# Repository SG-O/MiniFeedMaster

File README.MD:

# Mainboard for automated SMT Feeder system #

## Documentation ##

You can find the manufacturing documentation [here.](https://github.com/SG-O/MiniFeedMaster/tree/master/Doc)

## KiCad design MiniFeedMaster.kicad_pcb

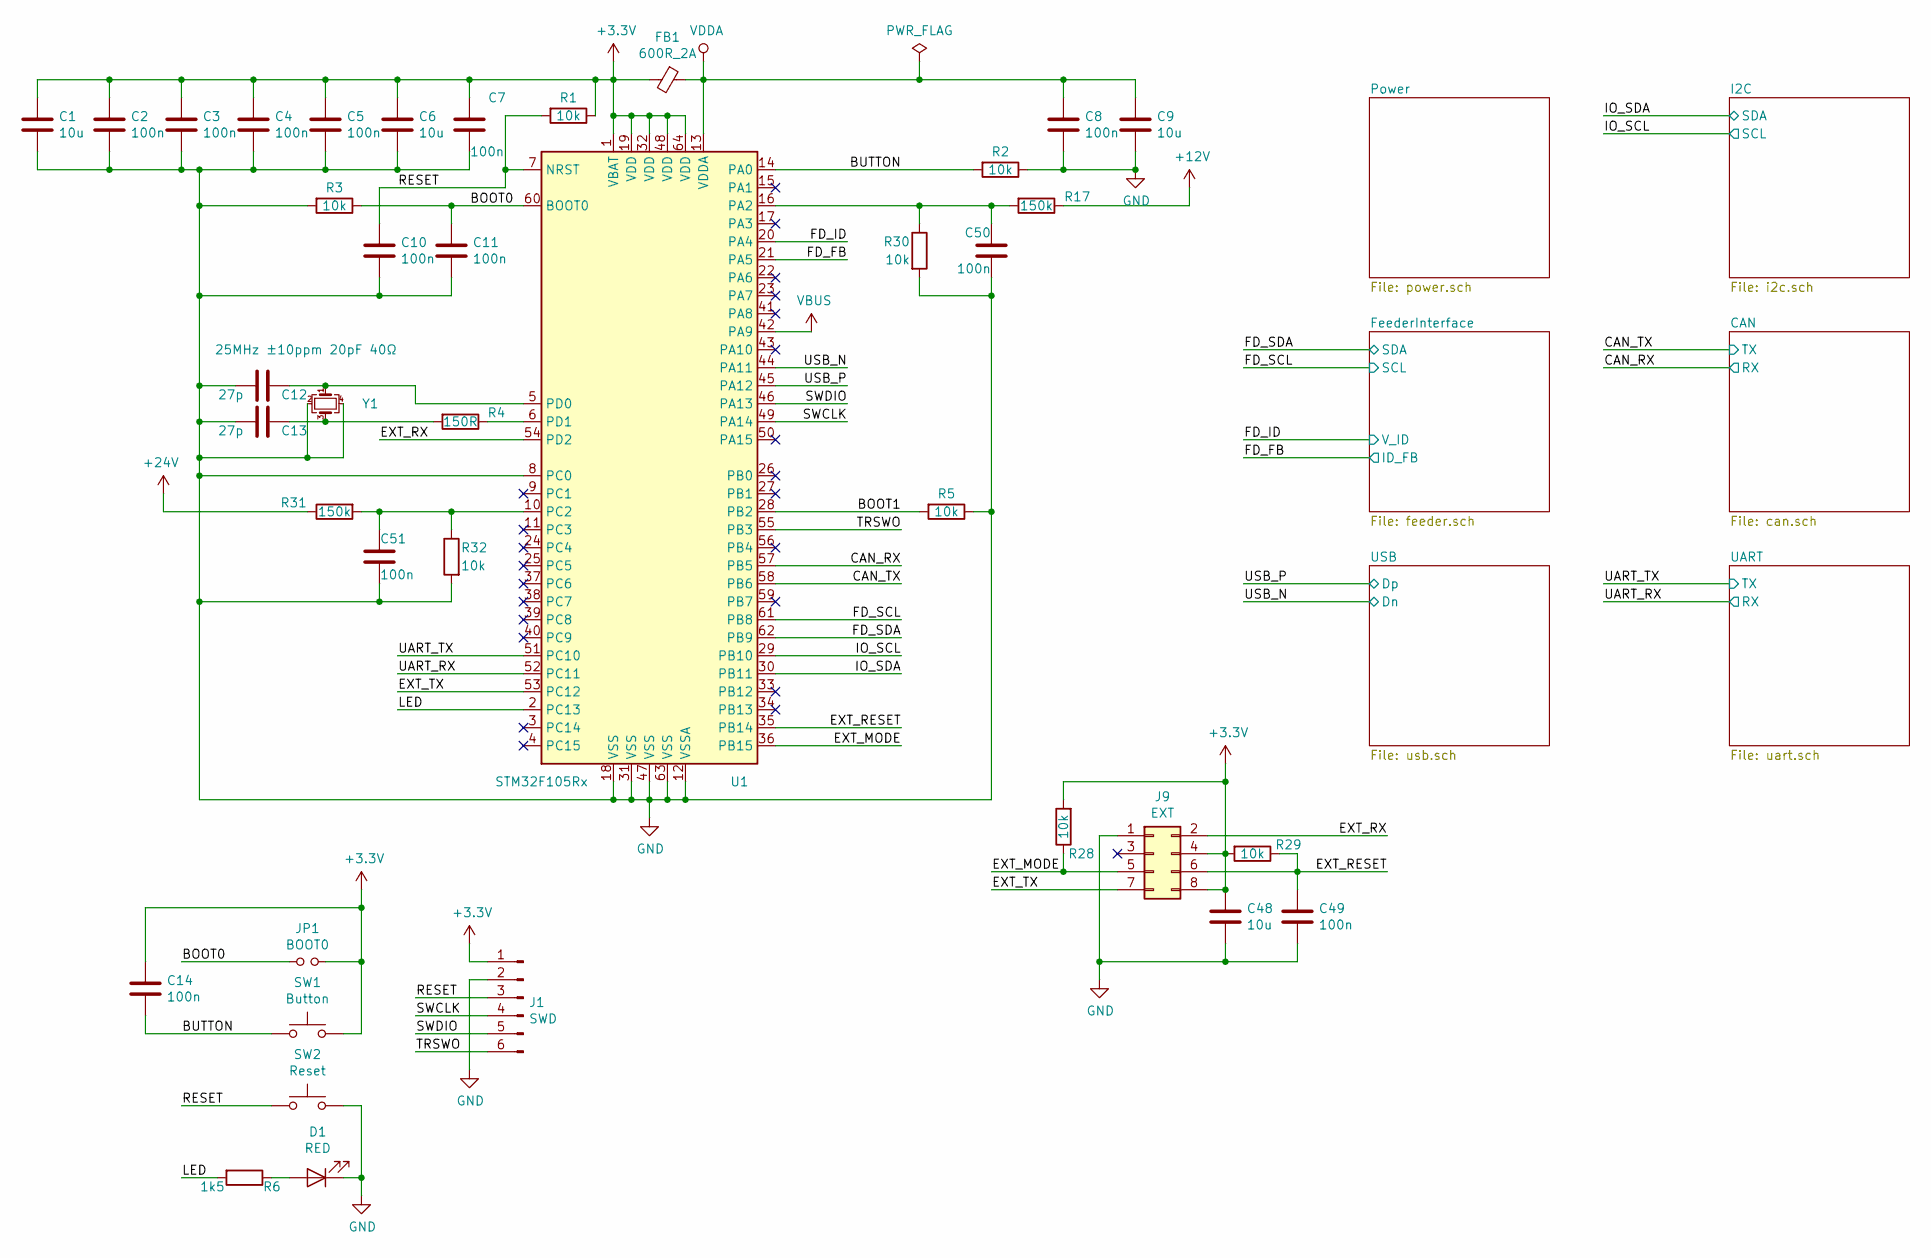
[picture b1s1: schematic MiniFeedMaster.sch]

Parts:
C1, C6, C9, C48: 10u; C_1206_3216Metric; lcsc# C14860
C2, C3, C4, C5, C7, C8, C10, C11, C14, C49, C50, C51: 100n; C_0603_1608Metric; lcsc# C1591
C12, C13: 27p; C_0603_1608Metric; lcsc# C107045
D1: RED; LED_0603_1608Metric; lcsc# C118330
FB1: 600R_2A; L_0805_2012Metric; lcsc# C81034
J1: SWD; PinSocket_1x06_P1.27mm_Vertical
J9: EXT; PinSocket_2x04_P2.54mm_Vertical; lcsc# C92271
JP1: BOOT0; SolderJumper-2_P1.3mm_Open_RoundedPad1.0x1.5mm
R1, R2, R3, R5, R28, R29, R30, R32: 10k; R_0603_1608Metric; lcsc# C128781
R4: 150R; R_0603_1608Metric; lcsc# C319856
R6: 1k5; R_0805_2012Metric; lcsc# C118217
R17, R31: 150k; R_0603_1608Metric; lcsc# C311920
SW1: Button; SW_SPST_SKQG_WithStem; lcsc# C318889
SW2: Reset; SW_SPST_SKQG_WithStem; lcsc# C318889
U1: STM32F105Rx; LQFP-64_10x10mm_P0.5mm; lcsc# C80986
Y1: 25MHz ±10ppm 20pF 40Ω; Crystal_SMD_3225-4Pin_3.2x2.5mm; lcsc# C709159

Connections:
+3V3: C1.1, C2.1, C3.1, C4.1, C5.1, C6.1, C7.1, C14.1, C48.1, FB1.2, J1.1, J9.4, J9.8, JP1.2, R1.1, R28.2, R29.2, SW1.2, U1.1 (VBAT), U1.19 (VDD), U1.32 (VDD), U1.48 (VDD), U1.64 (VDD); also elsewhere on the board
+12V: R17.1; also elsewhere on the board
+24V: R31.1; also elsewhere on the board
/BOOT0: C11.1, JP1.1, R3.1, U1.60 (BOOT0)
/BOOT1: R5.2, U1.28 (PB2)
/BUTTON: C14.2, R2.2, SW1.1, U1.14 (PA0)
/CAN_RX: U1.57 (PB5); also elsewhere on the board
/CAN_TX: U1.58 (PB6); also elsewhere on the board
/EXT_MODE: J9.5, R28.1, U1.36 (PB15)
/EXT_RESET: C49.1, J9.6, R29.1, U1.35 (PB14)
/EXT_RX: J9.2, U1.54 (PD2)
/EXT_TX: J9.7, U1.53 (PC12)
/FD_FB: U1.21 (PA5); also elsewhere on the board
/FD_ID: U1.20 (PA4); also elsewhere on the board
/FD_SCL: U1.61 (PB8); also elsewhere on the board
/FD_SDA: U1.62 (PB9); also elsewhere on the board
/IO_SCL: U1.29 (PB10); also elsewhere on the board
/IO_SDA: U1.30 (PB11); also elsewhere on the board
/LED: R6.2, U1.2 (PC13)
/RESET: C10.1, J1.3, R1.2, SW2.1, U1.7 (NRST)
/SWCLK: J1.4, U1.49 (PA14)
/SWDIO: J1.5, U1.46 (PA13)
/TRSWO: J1.6, U1.55 (PB3)
/UART_RX: U1.52 (PC11); also elsewhere on the board
/UART_TX: U1.51 (PC10); also elsewhere on the board
/USB_N: U1.44 (PA11); also elsewhere on the board
/USB_P: U1.45 (PA12); also elsewhere on the board
GND: C1.2, C2.2, C3.2, C4.2, C5.2, C6.2, C7.2, C8.2, C9.2, C10.2, C11.2, C12.2, C13.2, C48.2, C49.2, C50.2, C51.2, D1.1 (K), J1.2, J9.1, R2.1, R3.2, R5.1, R30.2, R32.2, SW2.2, U1.8 (PC0), U1.12 (VSSA), U1.18 (VSS), U1.31 (VSS), U1.47 (VSS), U1.63 (VSS), Y1.2, Y1.4; also elsewhere on the board
unnamed: C12.1, U1.5 (PD0), Y1.1
unnamed: C13.1, R4.2, Y1.3
unnamed: C50.1, R17.2, R30.1, U1.16 (PA2)
unnamed: C51.1, R31.2, R32.1, U1.10 (PC2)
unnamed: D1.2 (A), R6.1
unnamed: R4.1, U1.6 (PD1)
VBUS: U1.42 (PA9); also elsewhere on the board
VDDA: C8.1, C9.1, FB1.1, U1.13 (VDDA)

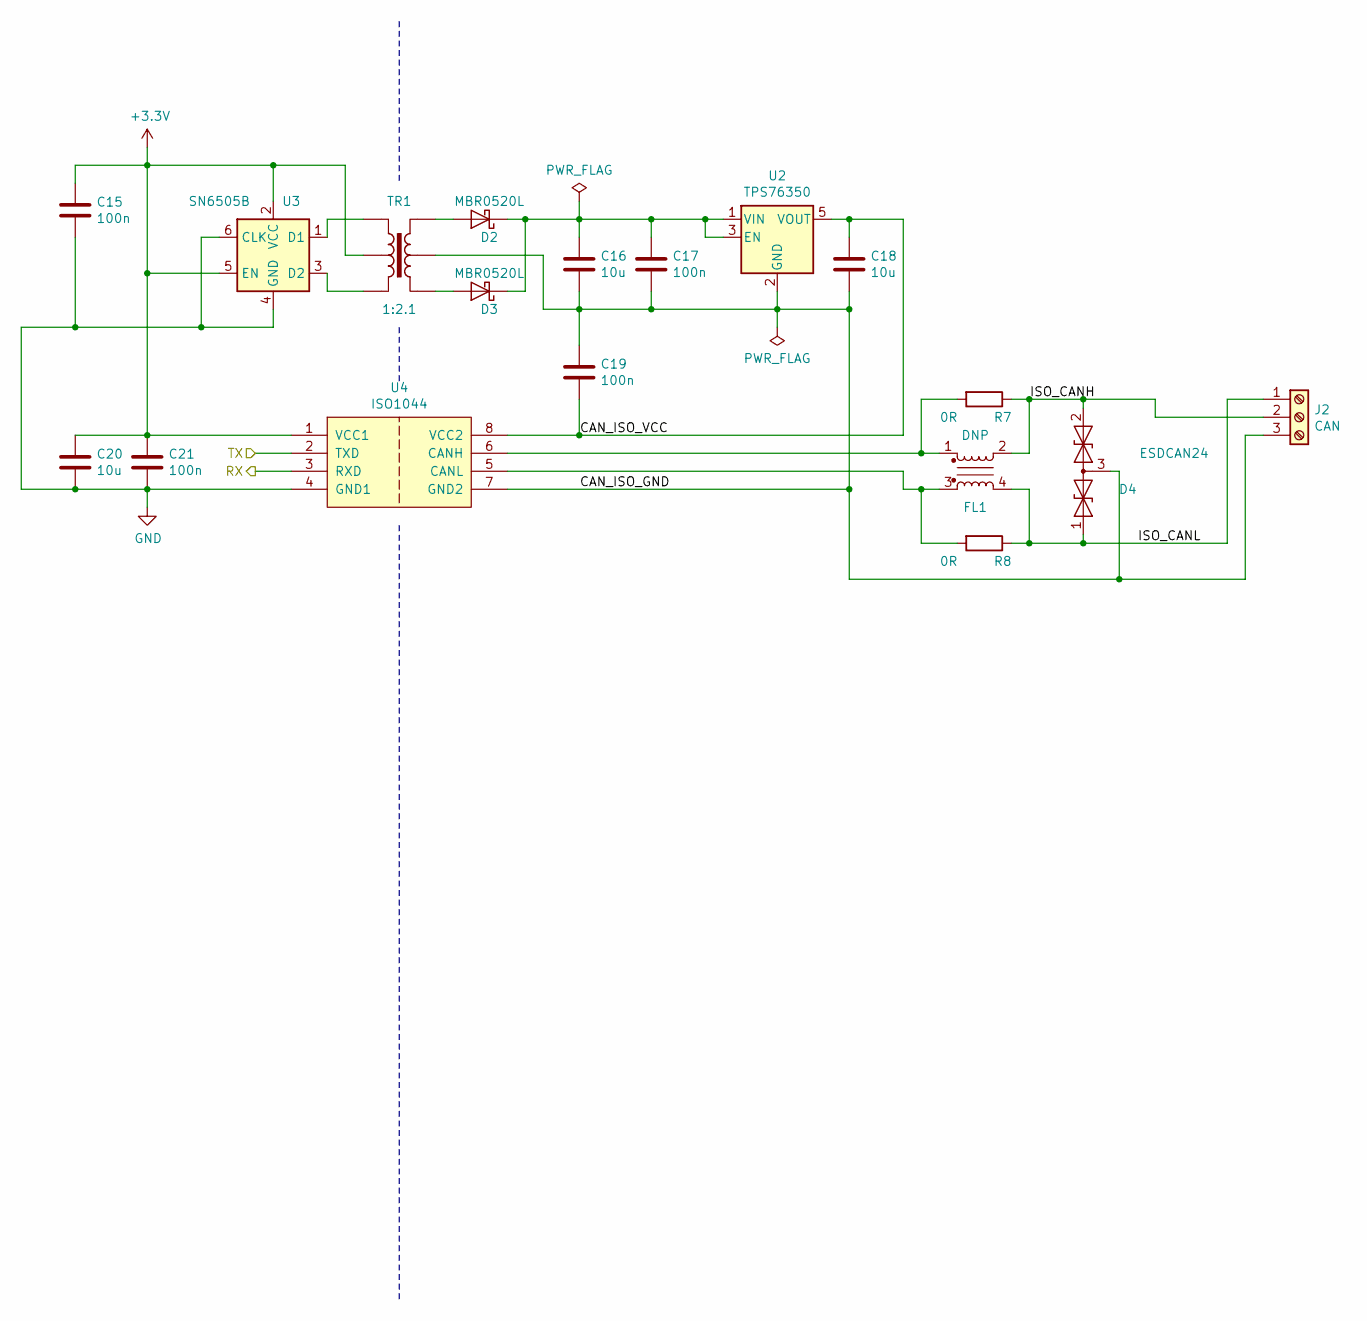
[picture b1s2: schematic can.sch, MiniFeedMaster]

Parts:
C15, C17, C19, C21: 100n; C_0603_1608Metric; lcsc# C1591
C16, C18, C20: 10u; C_1206_3216Metric; lcsc# C14860
D2, D3: MBR0520L; D_SOD-123; lcsc# C23848
D4: ESDCAN24; SOT-23; lcsc# C246766
FL1: DNP; FIL_ACT45B-510-2P-TL003; lcsc# C76584
J2: CAN; TerminalBlock_KaiFeng_KF141R-3_1x03_P2.54mm; lcsc# C475125
R7, R8: 0R; R_0603_1608Metric; lcsc# C163836
TR1: 1:2.1; TOROID_SMD_6PIN_(1109)
U2: TPS76350; SOT-23-5; lcsc# C194609
U3: SN6505B; SOT-23-6; lcsc# C74518
U4: ISO1044; SOIC-8_3.9x4.9mm_P1.27mm

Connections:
+3V3: C15.1, C20.1, C21.1, TR1.2, U3.2 (VCC), U3.5 (EN), U4.1 (VCC1); also elsewhere on the board
/CAN/CAN_ISO_GND: C16.2, C17.2, C18.2, C19.1, D4.3 (common), J2.3, TR1.5, U2.2 (GND), U4.7 (GND2)
/CAN/CAN_ISO_VCC: C18.1, C19.2, U2.5 (VOUT), U4.8 (VCC2)
/CAN/ISO_CANH: D4.2 (A2), FL1.2, J2.2, R7.1
/CAN/ISO_CANL: D4.1 (A1), FL1.4, J2.1, R8.1
/CAN_RX: U4.3 (RXD); also elsewhere on the board
/CAN_TX: U4.2 (TXD); also elsewhere on the board
GND: C15.2, C20.2, C21.2, U3.4 (GND), U3.6 (CLK), U4.4 (GND1); also elsewhere on the board
unnamed: C16.1, C17.1, D2.1 (K), D3.1 (K), U2.1 (VIN), U2.3 (EN)
unnamed: D2.2 (A), TR1.4
unnamed: D3.2 (A), TR1.6
unnamed: FL1.1, R7.2, U4.6 (CANH)
unnamed: FL1.3, R8.2, U4.5 (CANL)
unnamed: TR1.1, U3.3 (D2)
unnamed: TR1.3, U3.1 (D1)

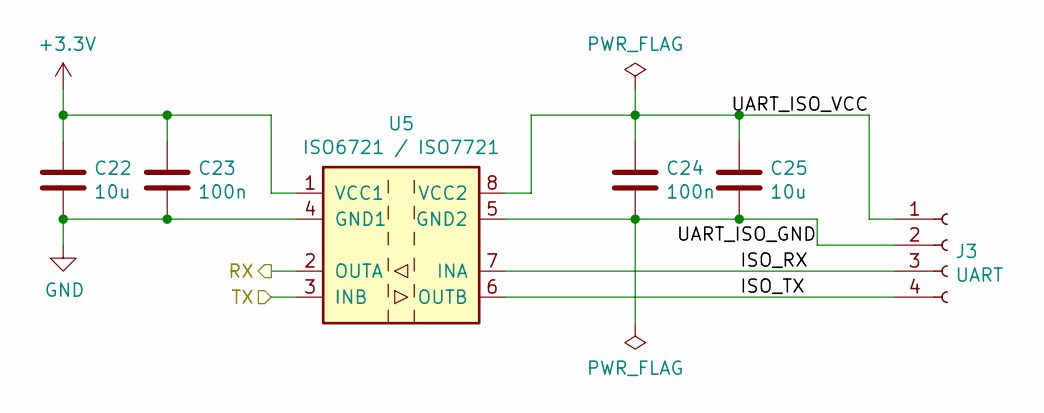
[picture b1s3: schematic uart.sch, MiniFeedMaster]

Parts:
C22, C25: 10u; C_1206_3216Metric; lcsc# C14860
C23, C24: 100n; C_0603_1608Metric; lcsc# C1591
J3: UART; TerminalBlock_KaiFeng_KF141R-4_1x04_P2.54mm; lcsc# C475126
U5: ISO6721 / ISO7721; SOIC-8_3.9x4.9mm_P1.27mm; lcsc# C366164

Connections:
+3V3: C22.1, C23.1, U5.1 (VCC1); also elsewhere on the board
/UART/ISO_RX: J3.3, U5.7 (INA)
/UART/ISO_TX: J3.4, U5.6 (OUTB)
/UART/UART_ISO_GND: C24.2, C25.2, J3.2, U5.5 (GND2)
/UART/UART_ISO_VCC: C24.1, C25.1, J3.1, U5.8 (VCC2)
/UART_RX: U5.2 (OUTA); also elsewhere on the board
/UART_TX: U5.3 (INB); also elsewhere on the board
GND: C22.2, C23.2, U5.4 (GND1); also elsewhere on the board

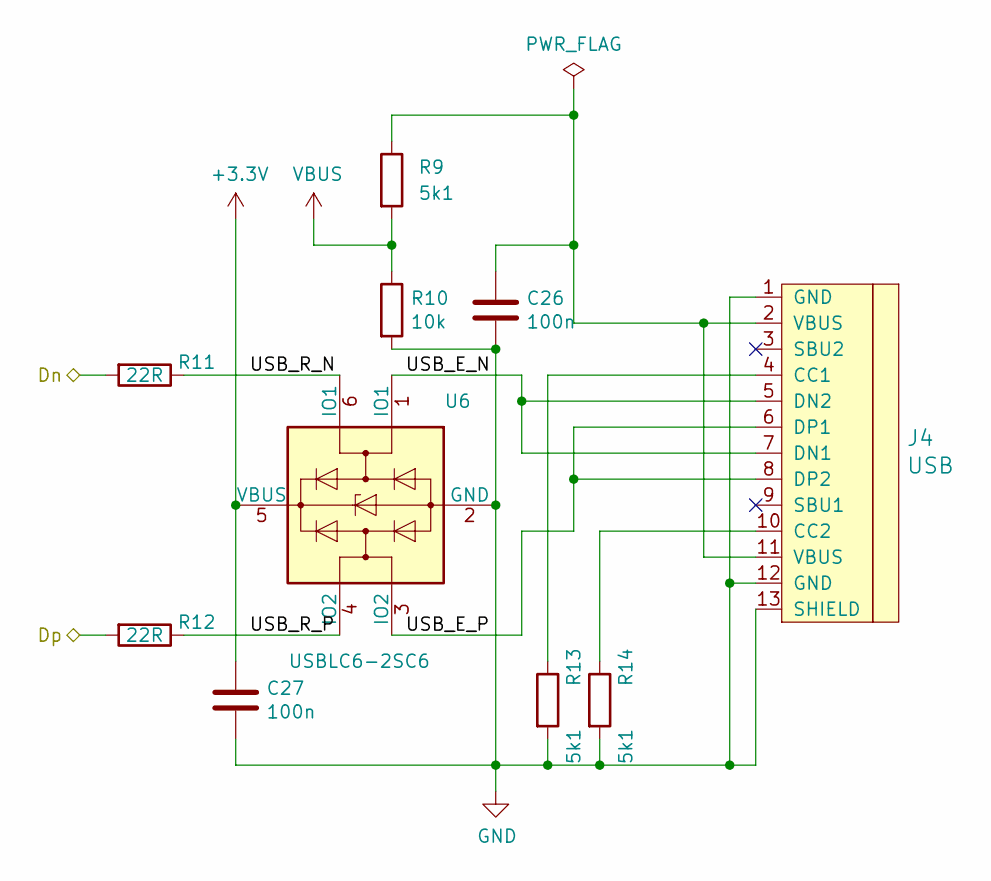
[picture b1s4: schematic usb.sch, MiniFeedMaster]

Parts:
C26, C27: 100n; C_0603_1608Metric; lcsc# C1591
J4: USB; HRO-TYPE-C-31-M-12-Assembly; lcsc# C165948
R9, R13, R14: 5k1; R_0603_1608Metric; lcsc# C425650
R10: 10k; R_0603_1608Metric; lcsc# C128781
R11, R12: 22R; R_0603_1608Metric; lcsc# C186356
U6: USBLC6-2SC6; SOT-23-6; lcsc# C558442

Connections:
+3V3: C27.1, U6.5 (VBUS); also elsewhere on the board
/USB/USB_E_N: J4.5 (DN2), J4.7 (DN1), U6.1 (IO1)
/USB/USB_E_P: J4.6 (DP1), J4.8 (DP2), U6.3 (IO2)
/USB/USB_R_N: R11.1, U6.6 (IO1)
/USB/USB_R_P: R12.1, U6.4 (IO2)
/USB_N: R11.2; also elsewhere on the board
/USB_P: R12.2; also elsewhere on the board
GND: C26.2, C27.2, J4.1 (GND), J4.12 (GND), J4.13 (SHIELD), R10.2, R13.2, R14.2, U6.2 (GND); also elsewhere on the board
unnamed: C26.1, J4.2 (VBUS), J4.11 (VBUS), R9.1
unnamed: J4.4 (CC1), R13.1
unnamed: J4.10 (CC2), R14.1
VBUS: R9.2, R10.1; also elsewhere on the board

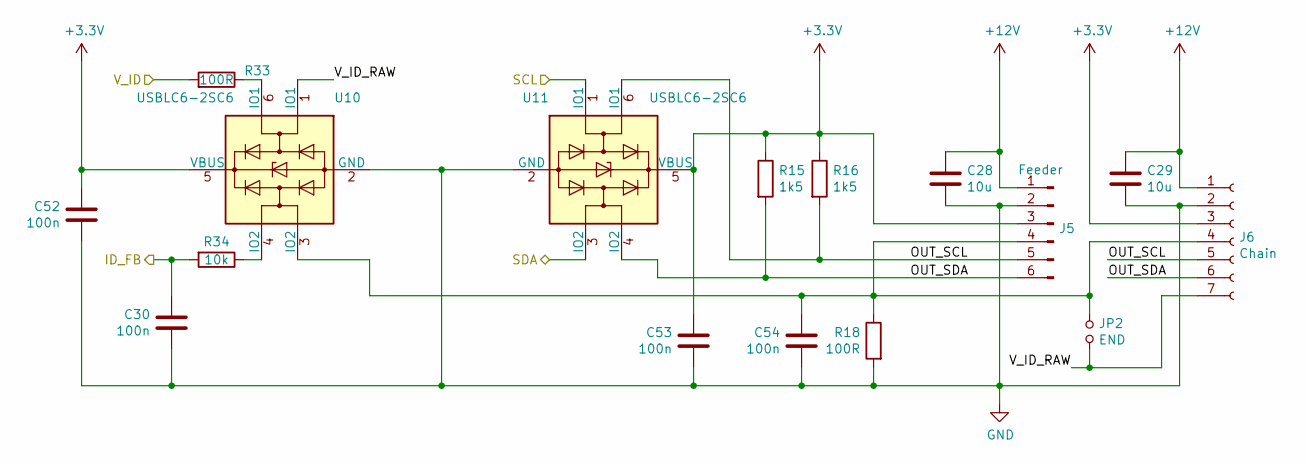
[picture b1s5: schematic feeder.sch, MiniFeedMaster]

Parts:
C28, C29: 10u; C_1206_3216Metric; lcsc# C14860
C30, C52, C53, C54: 100n; C_0603_1608Metric; lcsc# C1591
J5: Feeder; PogoEdgeConnector
J6: Chain; PinSocket_1x07_P2.54mm_Horizontal; lcsc# C225515
JP2: END; PinHeader_1x02_P2.54mm_Horizontal; lcsc# C376120;C5305
R15, R16: 1k5; R_0805_2012Metric; lcsc# C118217
R18, R33: 100R; R_0603_1608Metric; lcsc# C217683
R34: 10k; R_0603_1608Metric; lcsc# C128781
U10, U11: USBLC6-2SC6; SOT-23-6; lcsc# C558442

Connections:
+3V3: C52.1, C53.1, J5.3, J6.3, R15.1, R16.1, U10.5 (VBUS), U11.5 (VBUS); also elsewhere on the board
+12V: C28.1, C29.1, J5.1, J6.1; also elsewhere on the board
/FD_FB: C30.1, R34.2; also elsewhere on the board
/FD_ID: R33.2; also elsewhere on the board
/FD_SCL: U11.1 (IO1); also elsewhere on the board
/FD_SDA: U11.3 (IO2); also elsewhere on the board
/FeederInterface/OUT_SCL: J5.5, J6.5, R16.2, U11.6 (IO1)
/FeederInterface/OUT_SDA: J5.6, J6.6, R15.2, U11.4 (IO2)
/FeederInterface/V_ID_RAW: J6.7, JP2.2, U10.1 (IO1)
GND: C28.2, C29.2, C30.2, C52.2, C53.2, C54.2, J5.2, J6.2, R18.2, U10.2 (GND), U11.2 (GND); also elsewhere on the board
unnamed: C54.1, J5.4, J6.4, JP2.1, R18.1, U10.3 (IO2)
unnamed: R33.1, U10.6 (IO1)
unnamed: R34.1, U10.4 (IO2)

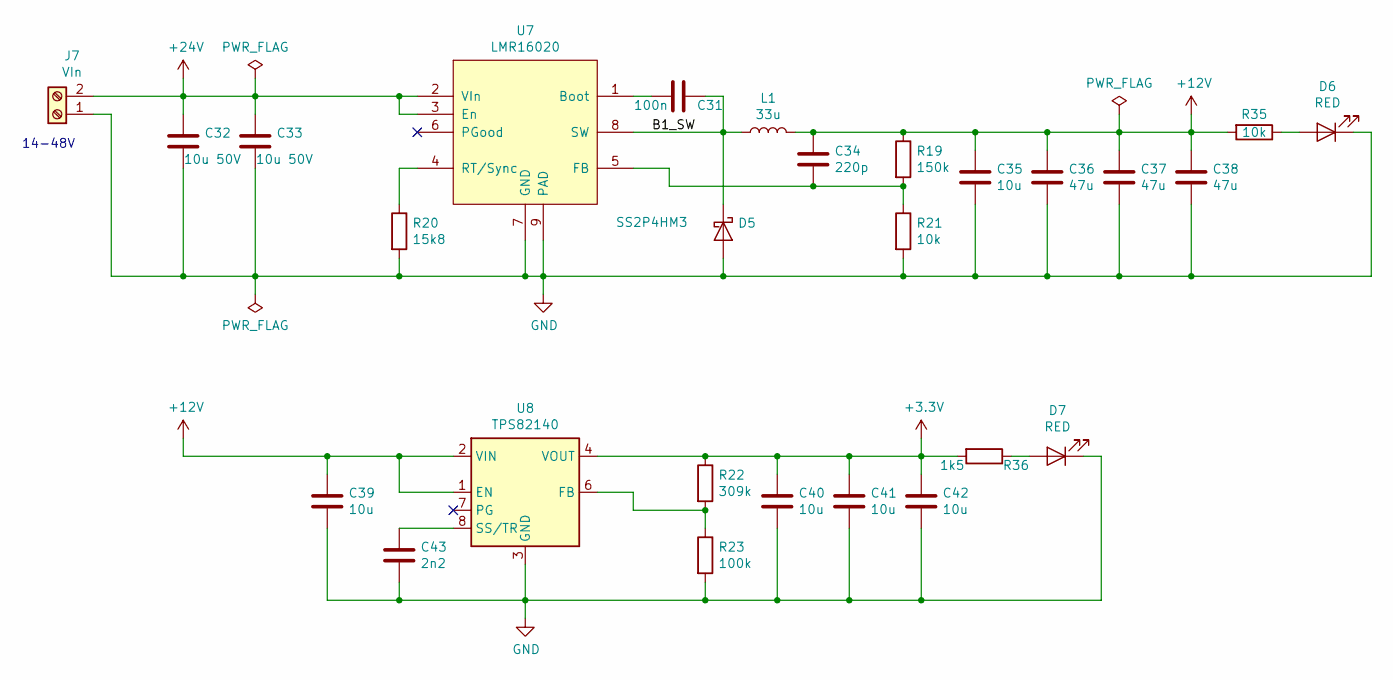
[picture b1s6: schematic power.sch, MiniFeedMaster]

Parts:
C31: 100n; C_0603_1608Metric; lcsc# C1591
C32, C33: 10u 50V; C_1210_3225Metric; lcsc# C337485
C34: 220p; C_0603_1608Metric; lcsc# C27675
C35, C39, C40, C41, C42: 10u; C_1206_3216Metric; lcsc# C14860
C36, C37, C38: 47u; C_2220_5650Metric; lcsc# C342293
C43: 2n2; C_0603_1608Metric; lcsc# C16033
D5: SS2P4HM3; DO-220AA; lcsc# C467996
D6, D7: RED; LED_0603_1608Metric; lcsc# C118330
J7: VIn; PhoenixContact_MC_1,5_2-G-3.81_1x02_P3.81mm_Horizontal; lcsc# C8387;C8466
L1: 33u; Inductor10x10mm; lcsc# C253612
R19: 150k; R_0603_1608Metric; lcsc# C311920
R20: 15k8; R_0603_1608Metric; lcsc# C149924
R21, R35: 10k; R_0603_1608Metric; lcsc# C128781
R22: 309k; R_0603_1608Metric; lcsc# C56054
R23: 100k; R_0603_1608Metric; lcsc# C133733
R36: 1k5; R_0805_2012Metric; lcsc# C118217
U7: LMR16020; SOIC-8-1EP_3.9x4.9mm_P1.27mm_EP2.41x3.3mm_ThermalVias; lcsc# C190006
U8: TPS82140; Texas_SIL0008D_MicroSiP-8-1EP_2.8x3mm_P0.65mm_EP1.1x1.9mm_T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; lcsc# C544385

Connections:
+3V3: C40.1, C41.1, C42.1, R22.1, R36.2, U8.4 (VOUT), U8.5 (VOUT); also elsewhere on the board
+12V: C34.1, C35.1, C36.1, C37.1, C38.1, C39.1, L1.2, R19.1, R35.2, U8.1 (EN), U8.2 (VIN); also elsewhere on the board
+24V: C32.1, C33.1, J7.2, U7.2 (VIn), U7.3 (En); also elsewhere on the board
/Power/B1_SW: C31.1, D5.1 (K), L1.1, U7.8 (SW)
GND: C32.2, C33.2, C35.2, C36.2, C37.2, C38.2, C39.2, C40.2, C41.2, C42.2, C43.2, D5.2 (A), D6.1 (K), D7.1 (K), J7.1, R20.2, R21.2, R23.2, U7.7 (GND), U7.9 (PAD), U8.3 (GND), U8.9 (GND); also elsewhere on the board
unnamed: C31.2, U7.1 (Boot)
unnamed: C34.2, R19.2, R21.1, U7.5 (FB)
unnamed: C43.1, U8.8 (SS/TR)
unnamed: D6.2 (A), R35.1
unnamed: D7.2 (A), R36.1
unnamed: R20.1, U7.4 (RT/Sync)
unnamed: R22.2, R23.1, U8.6 (FB)

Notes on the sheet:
14-48V

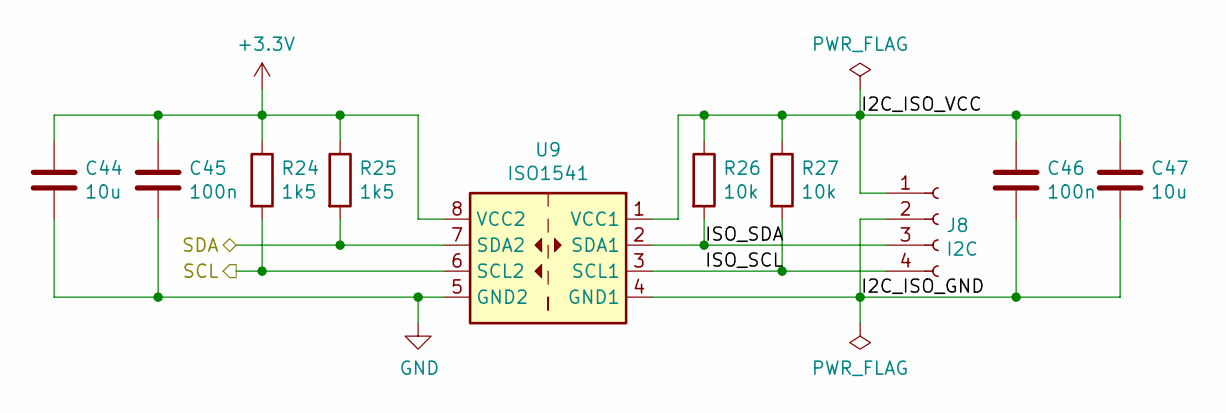
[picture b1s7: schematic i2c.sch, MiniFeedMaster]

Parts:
C44, C47: 10u; C_1206_3216Metric; lcsc# C14860
C45, C46: 100n; C_0603_1608Metric; lcsc# C1591
J8: I2C; TerminalBlock_KaiFeng_KF141R-4_1x04_P2.54mm; lcsc# C475126
R24, R25: 1k5; R_0805_2012Metric; lcsc# C118217
R26, R27: 10k; R_0603_1608Metric; lcsc# C128781
U9: ISO1541; SOIC-8_3.9x4.9mm_P1.27mm; lcsc# C143028

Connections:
+3V3: C44.1, C45.1, R24.1, R25.1, U9.8 (VCC2); also elsewhere on the board
/I2C/I2C_ISO_GND: C46.2, C47.2, J8.2, U9.4 (GND1)
/I2C/I2C_ISO_VCC: C46.1, C47.1, J8.1, R26.1, R27.1, U9.1 (VCC1)
/I2C/ISO_SCL: J8.4, R27.2, U9.3 (SCL1)
/I2C/ISO_SDA: J8.3, R26.2, U9.2 (SDA1)
/IO_SCL: R24.2, U9.6 (SCL2); also elsewhere on the board
/IO_SDA: R25.2, U9.7 (SDA2); also elsewhere on the board
GND: C44.2, C45.2, U9.5 (GND2); also elsewhere on the board

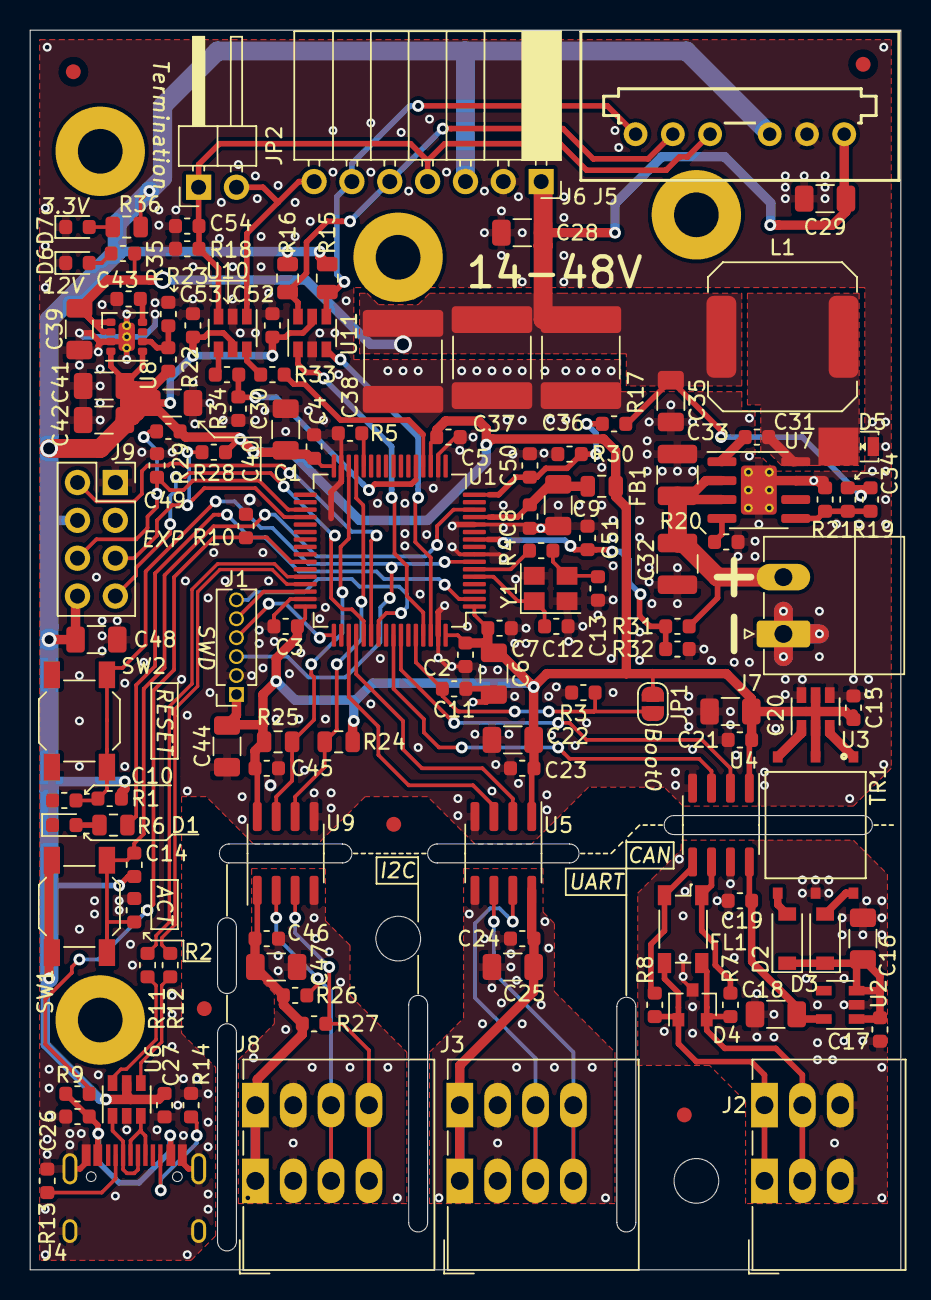
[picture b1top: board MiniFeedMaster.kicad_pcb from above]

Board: 2 copper layers, 58.4 x 83.2 mm, 131 parts (0 on the bottom side), 76 nets.

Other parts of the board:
Fid1, Fid2, Fid3, Fid4, Fid5: Fiducial_1mm_Mask2mm

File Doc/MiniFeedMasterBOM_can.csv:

Component,Description,Part,References,Value,Footprint,Quantity Per PCB,Datasheet,lcsc#,manf#,DNP
1,Unpolarized capacitor,C,C2 C3 C4 C5 C7 C8 C10 C11 C14 C15 C17 C19 C21 C23 C24 C26 C27 C30 C31 C45 C46 C49 C50 C51 C52 C53 C54,100n,C_0603_1608Metric,27,~,C1591,CL10B104KB8NNNC,
2,Unpolarized capacitor,C,C1 C6 C9 C16 C18 C20 C22 C25 C28 C29 C35 C39 C40 C41 C42 C44 C47 C48,10u,C_1206_3216Metric,18,~,C14860,CL31B106KAHNNNE,
3,Unpolarized capacitor,C,C32 C33,10u 50V,C_1210_3225Metric,2,~,C337485,UMK325AB7106KM-P,
4,Unpolarized capacitor,C,C34,220p,C_0603_1608Metric,1,~,C27675,CL10C221JB8NNNC,
5,Unpolarized capacitor,C,C12 C13,27p,C_0603_1608Metric,2,~,C107045,CC0603JRNPO9BN270,
6,Unpolarized capacitor,C,C43,2n2,C_0603_1608Metric,1,~,C16033,CL10B222KB8NNNC,
7,Unpolarized capacitor,C,C36 C37 C38,47u,C_2220_5650Metric,3,~,C342293,CGA9N3X7R1C476MT0Y0N,
8,"Bidirectional dual transient-voltage-suppression diode, center on pin 3",D_TVS_x2_AAC,D4,ESDCAN24,SOT-23,1,~,C246766,ESDCAN24-2BLY,
9,Schottky diode,D_Schottky,D2 D3,MBR0520L,D_SOD-123,2,~,C23848,MBR0520LT1G,
10,Light emitting diode,LED,D1 D6 D7,RED,LED_0603_1608Metric,3,~,C118330,D-060306R1/SS2/L,
11,Schottky diode,D_Schottky,D5,SS2P4HM3,DO-220AA,1,~,C467996,SS2P4HM3/84A,
12,"Ferrite bead, small symbol",Ferrite_Bead_Small,FB1,600R_2A,L_0805_2012Metric,1,~,C81034,MPZ2012S601ATD25,
13,"Generic screw terminal, single row, 01x03, script generated (kicad-library-utils/schlib/autogen/connector/)",Screw_Terminal_01x03,J2,CAN,TerminalBlock_KaiFeng_KF141R-3_1x03_P2.54mm,1,~,C475125,KF141R-2.54-3P,
14,"Generic connector, single row, 01x07, script generated (kicad-library-utils/schlib/autogen/connector/)",Conn_01x07_Female,J6,Chain,PinSocket_1x07_P2.54mm_Horizontal,1,~,C225515,A2541HWR-7P,
15,"Generic connector, double row, 02x04, odd/even pin numbering scheme (row 1 odd numbers, row 2 even numbers), script generated (kicad-library-utils/schlib/autogen/connector/)",Conn_02x04_Odd_Even,J9,EXT,PinSocket_2x04_P2.54mm_Vertical,1,~,C92271,DS1023-2*4SF11,
16,"Generic connector, single row, 01x06, script generated (kicad-library-utils/schlib/autogen/connector/)",Conn_01x06_Male,J5,Feeder,PogoEdgeConnector,1,~,,CUSTOM,
17,"Generic connector, single row, 01x06, script generated (kicad-library-utils/schlib/autogen/connector/)",Conn_01x06_Male,J1,SWD,PinSocket_1x06_P1.27mm_Vertical,1,~,,,DNP
18,"Generic connector, single row, 01x04, script generated (kicad-library-utils/schlib/autogen/connector/)",Conn_01x04_Female,J3 J8,UART,TerminalBlock_KaiFeng_KF141R-4_1x04_P2.54mm,2,~,C475126,KF141R-2.54-4P,
19,,HRO-TYPE-C-31-M-12,J4,USB,HRO-TYPE-C-31-M-12-Assembly,1,,C165948,TYPE-C-31-M-12,
20,"Generic screw terminal, single row, 01x02, script generated (kicad-library-utils/schlib/autogen/connector/)",Screw_Terminal_01x02,J7,VIn,"PhoenixContact_MC_1,5_2-G-3.81_1x02_P3.81mm_Horizontal",1,~,C8387;C8466,WJ15EDGRC-3.81-2P;WJ15EDGK-3.81-2P,
21,"Jumper, normally open, small symbol",Jumper_NO_Small,JP1,BOOT0,SolderJumper-2_P1.3mm_Open_RoundedPad1.0x1.5mm,1,~,,,DNP
22,"Jumper, normally open, small symbol",Jumper_NO_Small,JP2,END,PinHeader_1x02_P2.54mm_Horizontal,1,~,C376120;C5305,MTB125-1102R1;C5305,
23,Inductor,L,L1,33u,Inductor10x10mm,1,~,C253612,ABG10A50M330,
24,Resistor,R,R7 R8,0R,R_0603_1608Metric,2,~,C163836,WR06X0000FTL,
25,Resistor,R,R18 R33,100R,R_0603_1608Metric,2,~,C217683,ARG03FTC1000,
26,Resistor,R,R23,100k,R_0603_1608Metric,1,~,C133733,TC0325F1003T5E,
27,Resistor,R,R1 R2 R3 R5 R10 R21 R26 R27 R28 R29 R30 R32 R34 R35,10k,R_0603_1608Metric,14,~,C128781,TC0325F1002T5E,
28,Resistor,R,R4,150R,R_0603_1608Metric,1,~,C319856,AR03DTDX1500,
29,Resistor,R,R17 R19 R31,150k,R_0603_1608Metric,3,~,C311920,ARG03DTC1503,
30,Resistor,R,R20,15k8,R_0603_1608Metric,1,~,C149924,TR0603B15K8P0525Z,
31,Resistor,R,R6 R15 R16 R24 R25 R36,1k5,R_0805_2012Metric,6,~,C118217,TC0525F1501T5E,
32,Resistor,R,R11 R12,22R,R_0603_1608Metric,2,~,C186356,RN731JTTD22R0B25,
33,Resistor,R,R22,309k,R_0603_1608Metric,1,~,C56054,TC0325B3093T5E,
34,Resistor,R,R9 R13 R14,5k1,R_0603_1608Metric,3,~,C425650,TC0350F5101T5E,
35,"Push button switch, generic, two pins",SW_Push,SW1,Button,SW_SPST_SKQG_WithStem,1,~,C318889,TS-1187A-C-C-B,
36,"Push button switch, generic, two pins",SW_Push,SW2,Reset,SW_SPST_SKQG_WithStem,1,~,C318889,TS-1187A-C-C-B,
37,,TRANSF5,TR1,1:2.1,TOROID_SMD_6PIN_(1109),1,,,760390015,
38,,ISO1044,U4,ISO1044,SOIC-8_3.9x4.9mm_P1.27mm,1,https://www.ti.com/lit/ds/symlink/iso1044.pdf,,ISO1044BD,
39,"I2C Isolator, 2.5 kVrms, Unidirectional Clock, Bidirectional data, SOIC-8",ISO1541,U9,ISO1541,SOIC-8_3.9x4.9mm_P1.27mm,1,http://www.ti.com/lit/ds/symlink/iso1541.pdf,C143028,ISO1541DR,
40,"Low Power Dual-Channel 1/1 Digital Isolator, 25Mbps 33ns, Fail-Safe High, SO8",ISO7321C,U5,ISO6721 / ISO7721,SOIC-8_3.9x4.9mm_P1.27mm,1,https://www.ti.com/lit/ds/symlink/iso6721.pdf,C366164,ISO7721DR,
41,,LMR16020,U7,LMR16020,SOIC-8-1EP_3.9x4.9mm_P1.27mm_EP2.41x3.3mm_ThermalVias,1,https://www.ti.com/lit/ds/symlink/lmr16020.pdf?ts=1605917167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,C190006,LMR16020PDDAR,
42,"Low Noise, 1A, Transformer Drivers for Isolated Power Supplies, 160 kHz, SOT-23-6",SN6505ADBV,U3,SN6505B,SOT-23-6,1,http://www.ti.com/lit/ds/symlink/sn6505b.pdf,C74518,SN6505BDBVR,
43,"ARM Cortex-M3 MCU, 128KB flash, 64KB RAM, 72MHz, 2-3.6V, 51 GPIO, LQFP-64",STM32F105RBTx,U1,STM32F105Rx,LQFP-64_10x10mm_P0.5mm,1,http://www.st.com/st-web-ui/static/active/en/resource/techni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,C80986,STM32F105R8T6,
44,"Low power 150mA LDO 5.0V fixed output voltage, SOT-23-5",TPS76350,U2,TPS76350,SOT-23-5,1,http://www.ti.com/lit/ds/symlink/tps763.pdf,C194609,TPS76350DBVR,
45,"17V Input 2A Step-Down Converter MicroSiP Module with Integrated Inductor, μSiL-8",TPS82140,U8,TPS82140,Texas_SIL0008D_MicroSiP-8-1EP_2.8x3mm_P0.65mm_EP1.1x1.9mm_ThermalVias,1,http://www.ti.com/lit/ds/symlink/tps82140.pdf,C544385,TPS82140SILR,
46,"Bidirectional ESD Protection Diode, SOT-23-6",USBLC6-2SC6,U6 U10 U11,USBLC6-2SC6,SOT-23-6,3,http://www2.st.com/resource/en/datasheet/CD00050750.pdf,C558442,USBLC6-2SC6,
47,"Four pin crystal, GND on pins 2 and 4, small symbol",Crystal_GND24_Small,Y1,25MHz ±10ppm 20pF 40Ω,Crystal_SMD_3225-4Pin_3.2x2.5mm,1,~,C709159,CF4025M00020T8188048,
,,,,,,,,,,
,,,,,,,,,,
,,,,,,,,,,
,,,,,,,,,,
,,,,,,,,,,
Component Groups:,48,,,,,,,,,
Component Count:,126,,,,,,,,,
Fitted Components:,125,,,,,,,,,
Number of PCBs:,1,,,,,,,,,
Total components:,125,,,,,,,,,
Schematic Version:,v0.1-SNAPSHOT,,,,,,,,,
Schematic Date:,2020-11-21,,,,,,,,,
PCB Variant:,can,,,,,,,,,
BoM Date:,03.02.2021 23:28:12,,,,,,,,,
Schematic Source:,MiniFeedMaster.sch,,,,,,,,,
KiCad Version:,Eeschema (5.1.5)-3,,,,,,,,,

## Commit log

2021-01-04 Added License
2021-01-04 Changed mounting holes from 2.5mm to 3mm Changed some 0.2mm vias to 0.3mm.
2021-01-04 Fixed some references
2021-01-04 Changed some 0.2mm vias to 0.3mm
2021-02-02 Added IO Protection Switched Fault Signal to +3.3V Added Voltage sensing Added correct UART pins to EXT header
2021-02-03 Added LEDs to indicate power on the 12V and 3.3V rails Added Fiducials Moved references for SW1 and R2 Added 3D Model
2021-02-03 Added Readme
2021-02-03 Added position files
